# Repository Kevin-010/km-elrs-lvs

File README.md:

# km-elrs-lvs
A 2.4ghz ExpressLRS-compatible PWM receiver with integrated cell monitoring. KiCad project and related files.

This was created as a personal project to offset having used propreitary radio systems for several years prior (the previous truely usable open standard being PPM/FM): Suddenly (from my perspective) the community has an open source radio system and it also happens to be the best performing? I had to have one, so I made one.

Specs:
- ESP32 (PICO-V3) processor
- SX1280/1281 telemetry radio (direct 1x1, +12.5dBm) anything fancier isn't necessary for outdoor los on a small/medium plane (but more importantly would have been less likely to succeed when hand built)
- 1-3s (3.0-17v) input/servo power, with external brownout detector (the esp builtin one is problematic)
- 8 Channel PWM output, on standard servo pin headers
- JST GH CRSF/Serial/programming connector (similar to radiomaster cables)
- 7 channel voltage sense connector, measuring -5 to +35v (for 2-6s standard lipo balance plugs)

This not a beginner soldering project.  It is built similarly to most RC hardware - double sided with (almost) minimal compoent sizes crammed as close as possible to each other to save size and weight.  That said, it can be assembled by hand - I had no significant issues, although I recommend using at least a paste stencil.

The Wifi (ceramic tower) and ELRS (u.fl) footprints are made more interchangable for experimental purposes. As of version 1, the CRSF connector pinout is non-standard, due to an oversight (I thought it was downside up when I copied it from radiomaster's cable example). There are many test/cut points that could be removed to save space on a version 2 (none of the cut points were necessary, which is a great success, and why it's stuck at the first version)

Version 2 (Not yet tested) removes the test points, moves all components to the front side, fixes the CRSF pinout to match radiomaster cables, and uses larger clearances to allow a slightly cheaper pcb process.

Despite this project being built mostly a cathartic exercise, this has the unique (as of writing) feature of monitoring individual lithium cell voltages integrated into the receiver. This is the most common telemetry item I personally use on aircraft - Having it integrated, in addition to the weight/size reduction, is intended to increase the durability of combat aircraft (on which the cell sensor and interconnect is a common failure point), and otherwise reduce the chance for an aircraft to be missing its sensor. The cost is also theoretically lower than the equivalent two devices, since this only requires hardware integrated into the receiver cpu, but i'd have to sell them for that to actually make sense. This feature currently requires a small amount of custom software, see related repository (TODO LINK HERE).

Some footprints are Borrowed from other public hardware examples:
- https://github.com/crteensy/ELRS-8285-1280-5xPWM.git 
- https://github.com/AnyLeaf/elrs-hardware.git

To build firmware images for this and similar unsupported hardware, one can add an entry to ExpressLRS/targets/targets.json , after which platformio or elrs configurator in local mode can be used.
```
"km_lvs": {
                "product_name": "Kevin LVS 2.4GHz 8xPWM RX",
                "lua_name": "KM LVS",
                "layout_file": "elrs-lvs.json",
                "upload_methods": ["uart", "wifi"],
                "min_version": "3.3.0",
                "platform": "esp32",
                "firmware": "Unified_ESP32_2400_RX"
            },
```

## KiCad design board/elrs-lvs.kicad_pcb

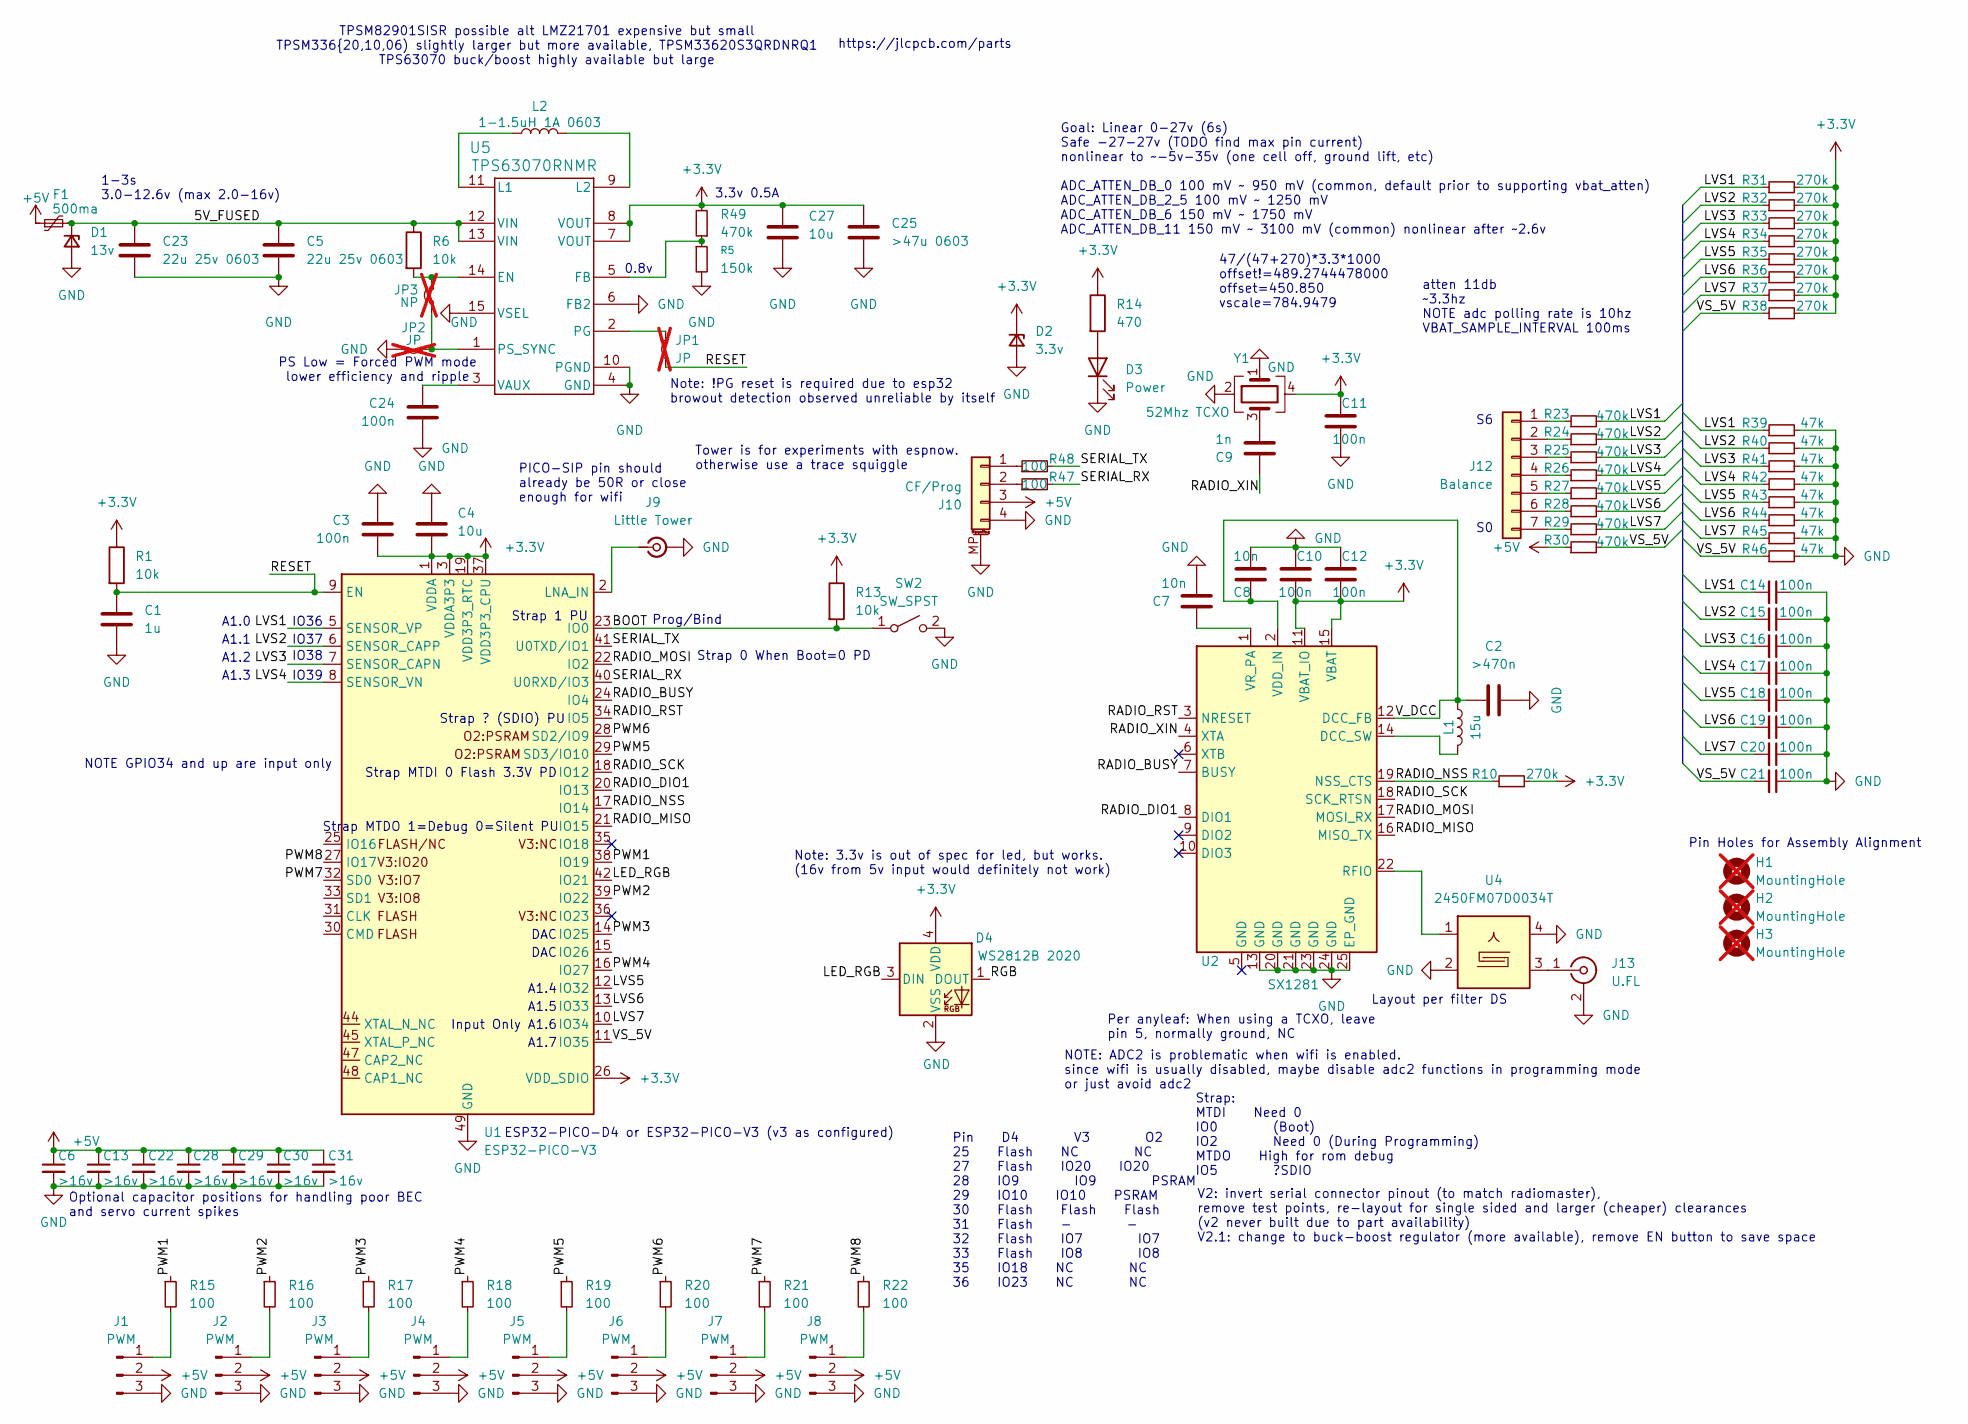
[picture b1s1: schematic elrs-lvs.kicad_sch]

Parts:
C1: 1u; C_0402_1005Metric; Part CL05A105MQ5NNNC; Digikey 1276-1235-1-ND
C2: >470n; C_0402_1005Metric; Part CL05A105MQ5NNNC; Digikey 1276-1235-1-ND
C3, C10, C11, C12, C24: 100n; C_0402_1005Metric; Part 0402B104K100CT; LCSC C100072
C4, C27: 10u; C_0402_1005Metric; Part GRM155R60J106ME05D; LCSC C15525
C5, C23: 22u 25v 0603; C_0603_1608Metric; Part KGM15CR51E226MT; Digikey 478-KGM15CR51E226MTCT-ND
C6, C13, C22, C29, C30, C31: >16v; C_0805-1206; Part TMK316BBJ226ML-T; Digikey 587-3246-1-ND
C7, C8: 10n; C_0402_1005Metric; Part CL05B103KB5NNNC; LCSC C15195
C9: 1n; C_0402_1005Metric; Part KGM05AR71H102KN; LCSC C2168479
C14, C15, C16, C17, C18, C19, C20, C21: 100n; C_0402_1005Metric; Part 0402B104K100CT; Digikey 1292-1629-1-ND
C25: >47u 0603; C_0603_1608Metric; Part C0603B476M007T; Digikey 4587-C0603B476M007TCT-ND
C28: >16v; C_1206_3216Metric; Part TMK316BBJ226ML-T; Digikey 587-3246-1-ND
D1: 13v; US2H_TOS; Part CUHZ12V,H3F; Digikey 264-CUHZ12VH3FCT-ND
D2: 3.3v; D_SOD-323; Part PJGBLC03-AU_R1_000A1; LCSC C6951951
D3: Power; LED_0603_1608Metric; Part LY Q976.01-Q1R2-36-1; LCSC C20562575
D4: WS2812B 2020; LED-WS2812B; Part WS2812B-2020; LCSC C965555
F1: 500ma; C_1210_3225Metric; Part SMD1210B075TF/24; LCSC C720078
H1, H2, H3: MountingHole; MountingHole_JLC; not fitted
J1, J2, J3, J4, J5, J6, J7, J8: PWM; PinHeader_1x03_P2.54mm_NoSilk; Part TSW-104-25-G-T-RA
J9: Little Tower; Molex_47948-0001_U.FL_Hirose_U.FL-R-SMT-1_Vertical; Part 47948-0001; Mouser 538-47948-0001
J10: CF/Prog; JST_GH_SM04B-GHS-TB_1x04-1MP_P1.25mm_Horizontal; Part SM04B-GHS-TB; LCSC C189895
J12: Balance; JST_XH_S7B-XH-A-1_1x07_P2.50mm_Horizontal_Zero_Clearance; Part S7B-XH-A-1; LCSC C491713
J13: U.FL; U.FL_Hirose_U.FL-R-SMT-1_Vertical_Molex_47948-0001; Part U.FL-R-SMT-1(80); LCSC C88374
JP1, JP2: JP; R_0201_0603_JP; Part CR0201-J/-000GLF; Digikey CR0201-J/-000GLFCT-ND; not fitted
JP3: NP; R_0201_0603_NP; Part CR0201-J/-000GLF; Digikey CR0201-J/-000GLFCT-ND; not fitted
L1: 15u; L_0805_2012Metric; Part MLZ2012M150W; LCSC C486333
L2: 1-1.5uH 1A 0603; L_0603_1608Metric; Part AOTA-B160808S1R0MT; Digikey 535-AOTA-B160808S1R0MTCT-ND
R1, R6, R13: 10k; R_0402_1005Metric; Part AC0402JR-0710KL; LCSC C144731
R5: 150k; R_0402_1005Metric; Part RT0402FRE07150KL; Digikey 13-RT0402FRE07150KLCT-ND
R10, R31, R32, R33, R34, R35, R36, R37, R38: 270k; R_0402_1005Metric; Part RC0402FR-07270KL; LCSC C163475
R14: 470; R_0402_1005Metric; Part AC0402JR-07470RL; LCSC C144711
R15, R16, R17, R18, R19, R20, R21, R22, R47, R48: 100; R_0402_1005Metric; Part AC0402JR-07100RL; LCSC C138288
R23, R24, R25, R26, R27, R28, R29, R30, R49: 470k; R_0402_1005Metric; Part RC0402DR-07470KL; LCSC C4001349
R39, R40, R41, R42, R43, R44, R45, R46: 47k; R_0402_1005Metric; Part RC0402FR-0747KL; LCSC C93943
SW2: SW_SPST; SW_CK_NANOT_AS; Part NANOT 100 AS; Digikey 108-NANOT100ASCT-ND
U1: ESP32-PICO-V3; QFN-48-1EP_7x7mm_P0.5mm_EP5.3x5.3mm; Part ESP32-PICO-V3; Mouser 356-ESP32-PICO-V3
U2: SX1281; QFN-24-1EP_4x4mm_P0.5mm_EP2.6x2.6mm; Part SX1281IMLTRT; Digikey SX1281IMLTRTTR-ND
U4: 2450FM07D0034T; 2450FM07D0034; Part 2450FM07D0034001T; Mouser 609-2450FM07D0034001 609-2450FM07D0034T
U5: TPS63070RNMR; RNM0015A; Part TPS63070RNMR; Digikey 296-44874-1-ND
Y1: 52Mhz TCXO; Crystal_SMD_2016-4Pin_2.0x1.6mm; Part ECS-TXO-20CSMV4-520-AN-TR; LCSC C22434896

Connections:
+3.3V: C3.2, C4.2, C10.2, C11.1, C12.2, C25.1, C27.1, D2.1 (K), D4.4 (VDD), R1.1, R10.2, R13.1, R14.1, R31.2, R32.2, R33.2, R34.2, R35.2, R36.2, R37.2, R38.2, R49.2, U1.1 (VDDA), U1.3 (VDDA3P3), U1.4 (VDDA3P3), U1.19 (VDD3P3_RTC), U1.26 (VDD_SDIO), U1.37 (VDD3P3_CPU), U1.43 (VDDA), U1.46 (VDDA), U2.11 (VBAT_IO), U2.15 (VBAT), U5.7 (VOUT), U5.8 (VOUT), Y1.4
+5V: C6.1, C13.1, C22.1, C28.1, C29.1, C30.1, C31.1, F1.1, J1.2, J2.2, J3.2, J4.2, J5.2, J6.2, J7.2, J8.2, J10.3, R30.1
/5V_FUSED: C5.1, C23.1, D1.1 (K), F1.2, R6.1, U5.12 (VIN), U5.13 (VIN)
/BOOT: R13.2, SW2.1 (A), U1.23 (IO0)
/LED_RGB: D4.3 (DIN), U1.42 (IO21)
/LVS1: C14.2, R23.2, R31.1, R39.1, U1.5 (SENSOR_VP)
/LVS2: C15.2, R24.2, R32.1, R40.1, U1.6 (SENSOR_CAPP)
/LVS3: C16.2, R25.2, R33.1, R41.1, U1.7 (SENSOR_CAPN)
/LVS4: C17.2, R26.2, R34.1, R42.1, U1.8 (SENSOR_VN)
/LVS5: C18.2, R27.2, R35.1, R43.1, U1.12 (IO32)
/LVS6: C19.2, R28.2, R36.1, R44.1, U1.13 (IO33)
/LVS7: C20.2, R29.2, R37.1, R45.1, U1.10 (IO34)
/PWM1: R15.1, U1.38 (IO19)
/PWM2: R16.1, U1.39 (IO22)
/PWM3: R17.1, U1.14 (IO25)
/PWM4: R18.1, U1.16 (IO27)
/PWM5: R19.1, U1.29 (SD3/IO10)
/PWM6: R20.1, U1.28 (SD2/IO9)
/PWM7: R21.1, U1.32 (SD0)
/PWM8: R22.1, U1.27 (IO17)
/RADIO_BUSY: U1.24 (IO4), U2.7 (BUSY)
/RADIO_DIO1: U1.20 (IO13), U2.8 (DIO1)
/RADIO_MISO: U1.21 (IO15), U2.16 (MISO_TX)
/RADIO_MOSI: U1.22 (IO2), U2.17 (MOSI_RX)
/RADIO_NSS: R10.1, U1.17 (IO14), U2.19 (NSS_CTS)
/RADIO_RST: U1.34 (IO5), U2.3 (NRESET)
/RADIO_SCK: U1.18 (IO12), U2.18 (SCK_RTSN)
/RADIO_XIN: C9.2, U2.4 (XTA)
/RESET: C1.1, JP1.1 (A), R1.2, U1.9 (EN)
/RGB: D4.1 (DOUT)
/SERIAL_RX: R47.2, U1.40 (U0RXD/IO3)
/SERIAL_TX: R48.2, U1.41 (U0TXD/IO1)
/VS_5V: C21.2, R30.2, R38.1, R46.1, U1.11 (IO35)
/V_DCC: C2.1, C8.2, L1.1, U2.2 (VDD_IN), U2.12 (DCC_FB)
GND: C1.2, C2.2, C3.1, C4.1, C5.2, C6.2, C7.1, C8.1, C10.1, C11.2, C12.1, C13.2, C14.1, C15.1, C16.1, C17.1, C18.1, C19.1, C20.1, C21.1, C22.2, C23.2, C24.2, C25.2, C27.2, C28.2, C29.2, C30.2, C31.2, D1.2 (A), D2.2 (A), D3.1 (K), D4.2 (VSS), J1.3, J2.3, J3.3, J4.3, J5.3, J6.3, J7.3, J8.3, J9.2 (Ext), J10.4, J10.MP (MountPin), J13.2 (Ext), JP2.2 (B), R5.2, R39.2, R40.2, R41.2, R42.2, R43.2, R44.2, R45.2, R46.2, SW2.2 (B), U1.49 (GND), U2.13 (GND), U2.20 (GND), U2.21 (GND), U2.23 (GND), U2.24 (GND), U2.25 (EP_GND), U4.2, U4.4, U5.4 (GND), U5.6 (FB2), U5.10 (PGND), U5.15 (VSEL), Y1.1, Y1.2
unnamed: C9.1, Y1.3
unnamed: D3.2 (A), R14.2
unnamed: J1.1, R15.2
unnamed: J2.1, R16.2
unnamed: J3.1, R17.2
unnamed: J4.1, R18.2
unnamed: J5.1, R19.2
unnamed: J6.1, R20.2
unnamed: J7.1, R21.2
unnamed: J8.1, R22.2
unnamed: J9.1 (In), U1.2 (LNA_IN)
unnamed: J10.1, R48.1
unnamed: J10.2, R47.1
unnamed: J12.1, R23.1
unnamed: J12.2, R24.1
unnamed: J12.3, R25.1
unnamed: J12.4, R26.1
unnamed: J12.5, R27.1
unnamed: J12.6, R28.1
unnamed: J12.7, R29.1
unnamed: J13.1 (In), U4.3
unnamed: JP1.2 (B), U5.2 (PG)
unnamed: JP2.1 (A), JP3.1 (A), U5.1 (PS_SYNC)
unnamed: JP3.2 (B), R6.2, U5.14 (EN)
unnamed: L1.2, U2.14 (DCC_SW)
unnamed: U2.22 (RFIO), U4.1
unnamed: C7.2, U2.1 (VR_PA)
unnamed: R5.1, R49.1, U5.5 (FB)
unnamed: L2.1, U5.11 (L1)
unnamed: L2.2, U5.9 (L2)
unnamed: C24.1, U5.3 (VAUX)

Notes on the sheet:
Goal: Linear 0-27v (6s) Safe -27-27v (TODO find max pin current) nonlinear to ~-5v-35v (one cell off, ground lift, etc) ADC_ATTEN_DB_0 100 mV ~ 950 mV (common, default prior to supporting vbat_atten) ADC_ATTEN_DB_2_5 100 mV ~ 1250 mV ADC_ATTEN_DB_6 150 mV ~ 1750 mV ADC_ATTEN_DB_11 150 mV ~ 3100 mV 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
IO37
PICO-SIP pin should already be 50R or close enough for wifi
A1.4
V2: invert serial connector pinout (to match radiomaster), remove test points, re-layout for single sided and larger (cheaper) clearances (v2 never built due to part availability) V2.1: change to buck-boost regulator (more available), remove EN button to save space
A1.7
IO39
Strap MTDO 1=Debug 0=Silent PU
https://jlcpcb.com/parts
A1.2
Input Only A1.6
NOTE: ADC2 is problematic when wifi is enabled. since wifi is usually disabled, maybe disable adc2 functions in programming mode or just avoid adc2
IO36
A1.3
1-3s 3.0-12.6v (max 2.0-16v)
Pin Holes for Assembly Alignment
Strap 0 When Boot=0 PD
47/(47+270)*3.3*1000 offset!=489.2744478000 offset=450.850 vscale=784.9479
Strap ? (SDIO) PU
0.8v
Pin D4 V3 O2 25 Flash NC NC 27 Flash IO20 IO20 28 IO9 IO9 PSRAM 29 IO10 IO10 PSRAM 30 Flash Flash Flash 31 Flash - - 32 Flash IO7 IO7 33 Flash IO8 IO8 35 IO18 NC NC 36 IO23 NC NC
Strap MTDI 0 Flash 3.3V PD
IO38
Per anyleaf: When using a TCXO, leave pin 5, normally ground, NC
3.3v 0.5A
Note: !PG reset is required due to esp32 browout detection observed unreliable by itself
Optional capacitor positions for handling poor BEC and servo current spikes
TPSM82901SISR possible alt LMZ21701 expensive but small TPSM336{20,10,06) slightly larger but more available, TPSM33620S3QRDNRQ1 TPS63070 buck/boost highly available but large
A1.0
Prog/Bind
Layout per filter DS
Note: 3.3v is out of spec for led, but works. (16v from 5v input would definitely not work)
Strap: MTDI Need 0 IO0 (Boot) IO2 Need 0 (During Programming) MTDO High for rom debug IO5 ?SDIO
NOTE GPIO34 and up are input only
atten 11db ~3.3hz NOTE adc polling rate is 10hz VBAT_SAMPLE_INTERVAL 100ms
Strap 1 PU
A1.1
DAC
ESP32-PICO-D4 or ESP32-PICO-V3 (v3 as configured)
Tower is for experiments with espnow. otherwise use a trace squiggle

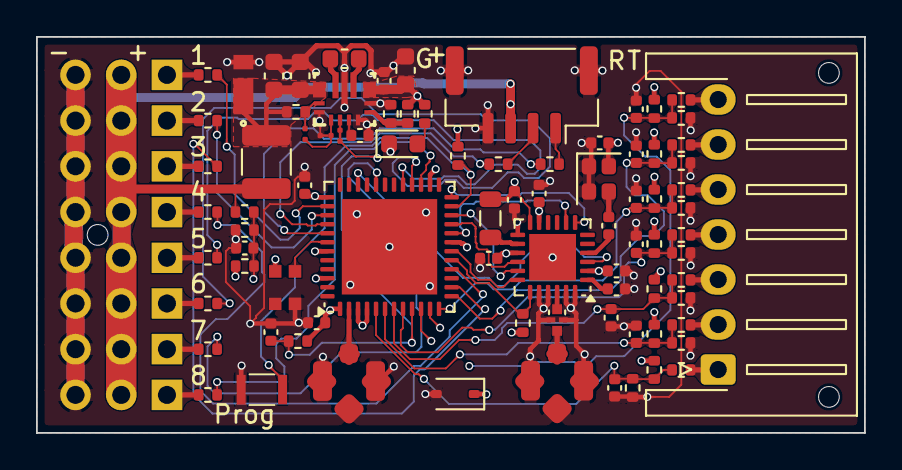
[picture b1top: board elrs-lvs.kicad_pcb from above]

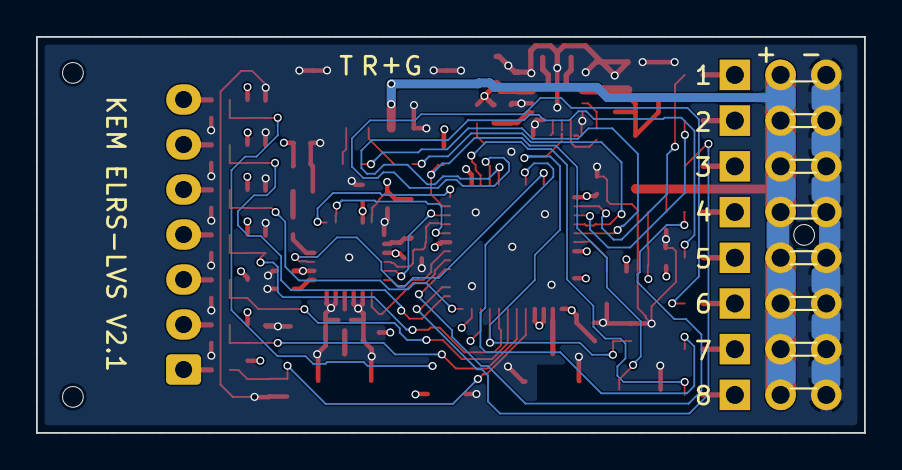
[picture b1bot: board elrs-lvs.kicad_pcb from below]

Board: 4 copper layers, 46.0 x 22.0 mm, 102 parts (8 on the bottom side), 65 nets.

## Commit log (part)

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2025-07-03 Initial project files copy, at V1
2026-03-05 update to kicad version 9 format. no changes.
2026-03-05 invert serial connector pinout
2026-03-05 remove dnp options and test points
2026-03-05 update library footprints
2026-03-08 initial placement for single sided lower density
2026-03-10 routing prior to starting over with rotation
2026-03-10 rotate and initial route
2026-03-10 cleanup
2026-03-10 export for review
2026-03-10 update readme for v2 changes
2026-03-10 more cleanup
2026-03-12 change D2 to unidirectional, add most lcsc numbers (alternates needed for some parts)
2026-03-12 label adjustment and some footprint drc fixes
2026-03-12 mess stuff up for investigating jlc pcba
